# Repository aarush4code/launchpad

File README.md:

I created a macropad, that can:
- higher and lower the volume
- copy and paste
- enter
- pause.

Whilecreating this, I learned how to wire, route, and CAD things in Fusion360. This project has been very fun as making a macropad in something I have never done before.

## Bill of Materials (BOM)
Here is the list of physical materials for launchpad:

- 1x Seeed Studio XIAO RP2040
- 6x Cherry MX Switches
- 6x DSA Keycaps
- 6x SK6812 MINI-E LEDs
- 4x M3x16mm Screws
- 4x M3x5mm Heatset Inserts
- 1x 3D-printed case (with 2 pieces)

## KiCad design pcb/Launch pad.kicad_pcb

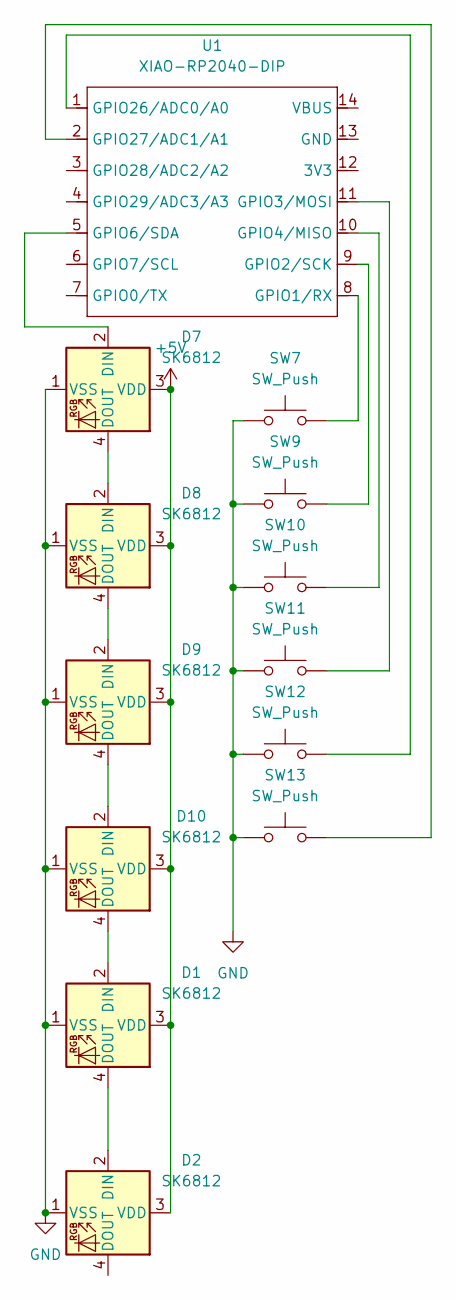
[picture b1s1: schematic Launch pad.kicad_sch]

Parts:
D1, D2, D7, D8, D9, D10: SK6812; LED_SK6812_PLCC4_5.0x5.0mm_P3.2mm
SW7, SW9, SW10, SW11, SW12, SW13: SW_Push; SW_Cherry_MX_1.00u_PCB
U1: XIAO-RP2040-DIP

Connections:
+5V: D1.3 (VDD), D2.3 (VDD), D7.3 (VDD), D8.3 (VDD), D9.3 (VDD), D10.3 (VDD)
GND: D1.1 (VSS), D2.1 (VSS), D7.1 (VSS), D8.1 (VSS), D9.1 (VSS), D10.1 (VSS), SW7.1, SW9.1, SW10.1, SW11.1, SW12.1, SW13.1
unnamed: D1.2 (DIN), D10.4 (DOUT)
unnamed: D1.4 (DOUT), D2.2 (DIN)
unnamed: D7.2 (DIN), U1.5 (GPIO6/SDA)
unnamed: D7.4 (DOUT), D8.2 (DIN)
unnamed: D8.4 (DOUT), D9.2 (DIN)
unnamed: D9.4 (DOUT), D10.2 (DIN)
unnamed: SW7.2, U1.8 (GPIO1/RX)
unnamed: SW9.2, U1.9 (GPIO2/SCK)
unnamed: SW11.2, U1.11 (GPIO3/MOSI)
unnamed: SW10.2, U1.10 (GPIO4/MISO)
unnamed: SW12.2, U1.1 (GPIO26/ADC0/A0)
unnamed: SW13.2, U1.2 (GPIO27/ADC1/A1)

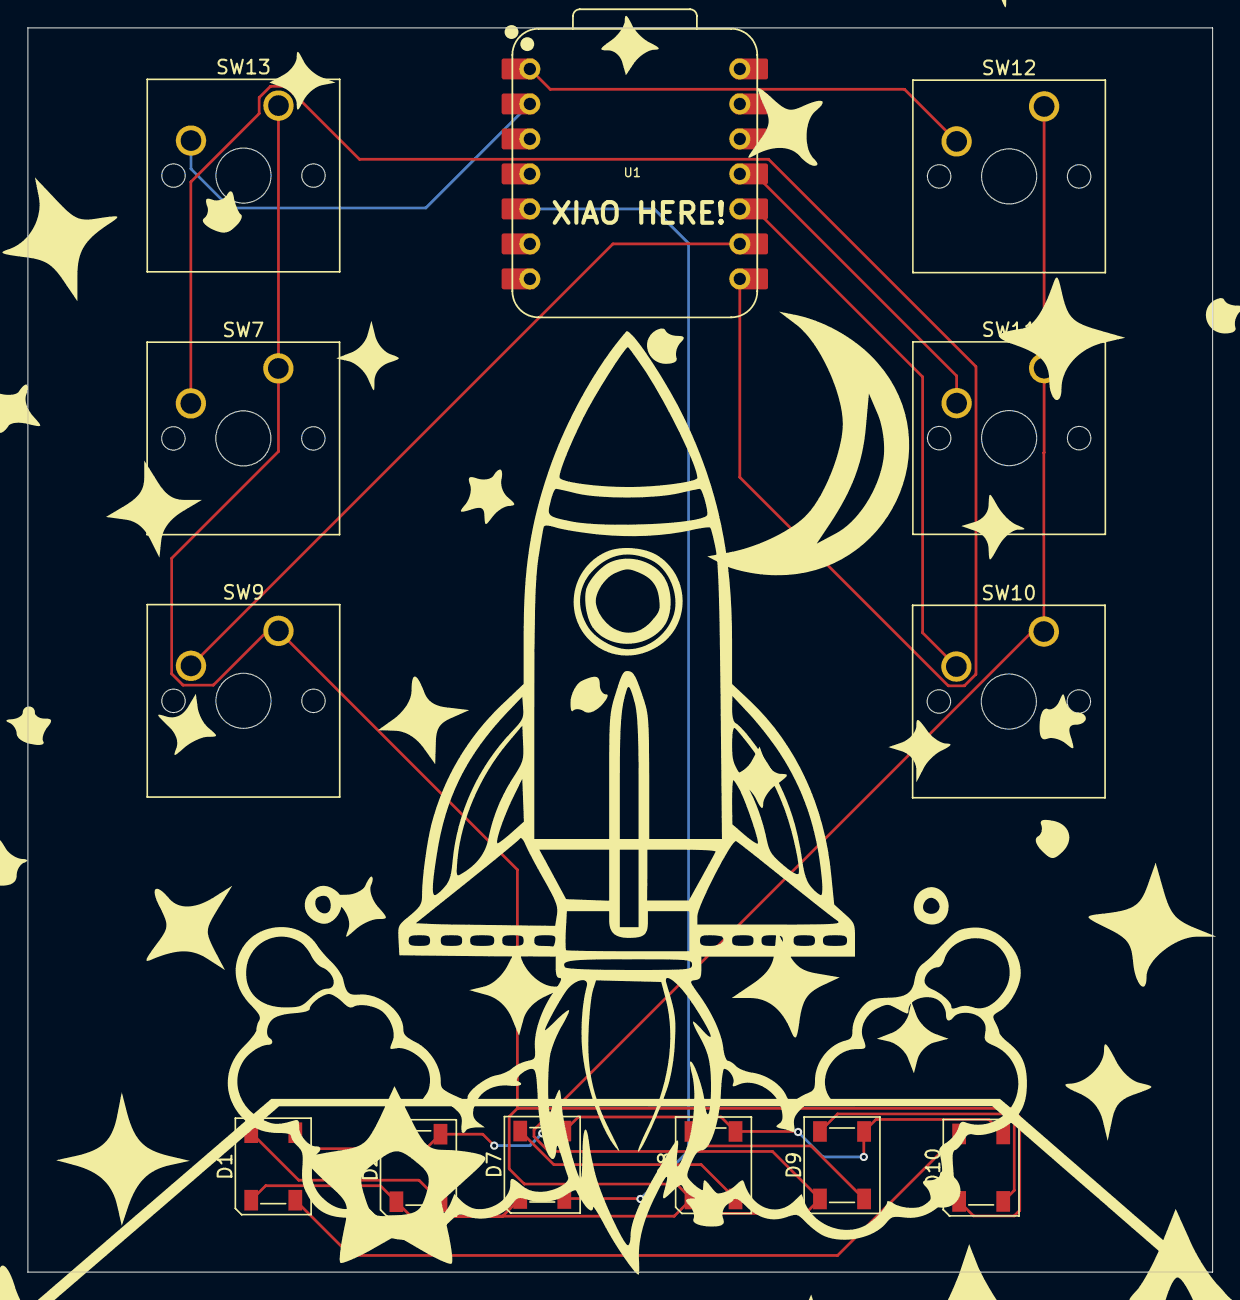
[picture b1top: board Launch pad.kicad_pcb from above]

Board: 2 copper layers, 86.0 x 90.3 mm, 13 parts (0 on the bottom side), 14 nets.

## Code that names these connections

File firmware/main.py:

# These are imports from the kmk library
from kmk.kmk_keyboard import KMKKeyboard
from kmk.scanners.keypad import KeysScanner
from kmk.keys import KC
from kmk.extensions.RGB import RGB, AnimationsModes
from kmk.modules.macros import Press, Release, Tap, Macros

# This is the main instance of your keyboard
keyboard = KMKKeyboard()

# Add the macro extension
macros = Macros()
keyboard.modules.append(macros)

# Define your pins here!
PINS = [board.GPIO3, board.GPIO4, board.GPIO2, board.GPIO1, board.GPIO6,board.GPIO26, board.GPIO27]

# Tell kmk we are not using a key matrix
keyboard.matrix = KeysScanner(
    pins=PINS,
    value_when_pressed=False,
)


rgb = RGB(
    pixel_pin=board.GPIO6,
    num_pixel=6,
    hue_default=0,
    animation_mode=AnimationsModes.STATIC,
    sat_default=0,
)
keyboard.extensions.append(rgb)
 
# Here you define the buttons corresponding to the pins
# Look here for keycodes: https://github.com/KMKfw/kmk_firmware/blob/main/docs/en/keycodes.md
# And here for macros: https://github.com/KMKfw/kmk_firmware/blob/main/docs/en/macros.md
keyboard.keymap = [
    [KC.ENTER,KC.MACRO(Press(KC.LCTRL), Tap(KC.V), Release(KC.LCTRL)), 
    KC.MACRO(Press(KC.LCTRL), Tap(KC.C), Release(KC.LCTRL)),KC.MEDIA_PLAY_PAUSE, 
    KC.VOLU, KC.VOLD]
]

# Start kmk!
if __name__ == '__main__':
    keyboard.go()

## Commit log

2025-11-26 file organization
2025-11-26 rename launchpad backups
2025-11-26 update launchpad folder name
2025-11-26 remove launchpad folder from git repo
2025-11-26 removing other extra files from repo
2025-11-26 removed gitattributes from repo as well
2025-11-26 added cad and firmware folders
2025-11-27 added firmware
2025-11-27 added cad file complete
